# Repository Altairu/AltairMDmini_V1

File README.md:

# AltairMDmini_V1
AltairMDmini_V1

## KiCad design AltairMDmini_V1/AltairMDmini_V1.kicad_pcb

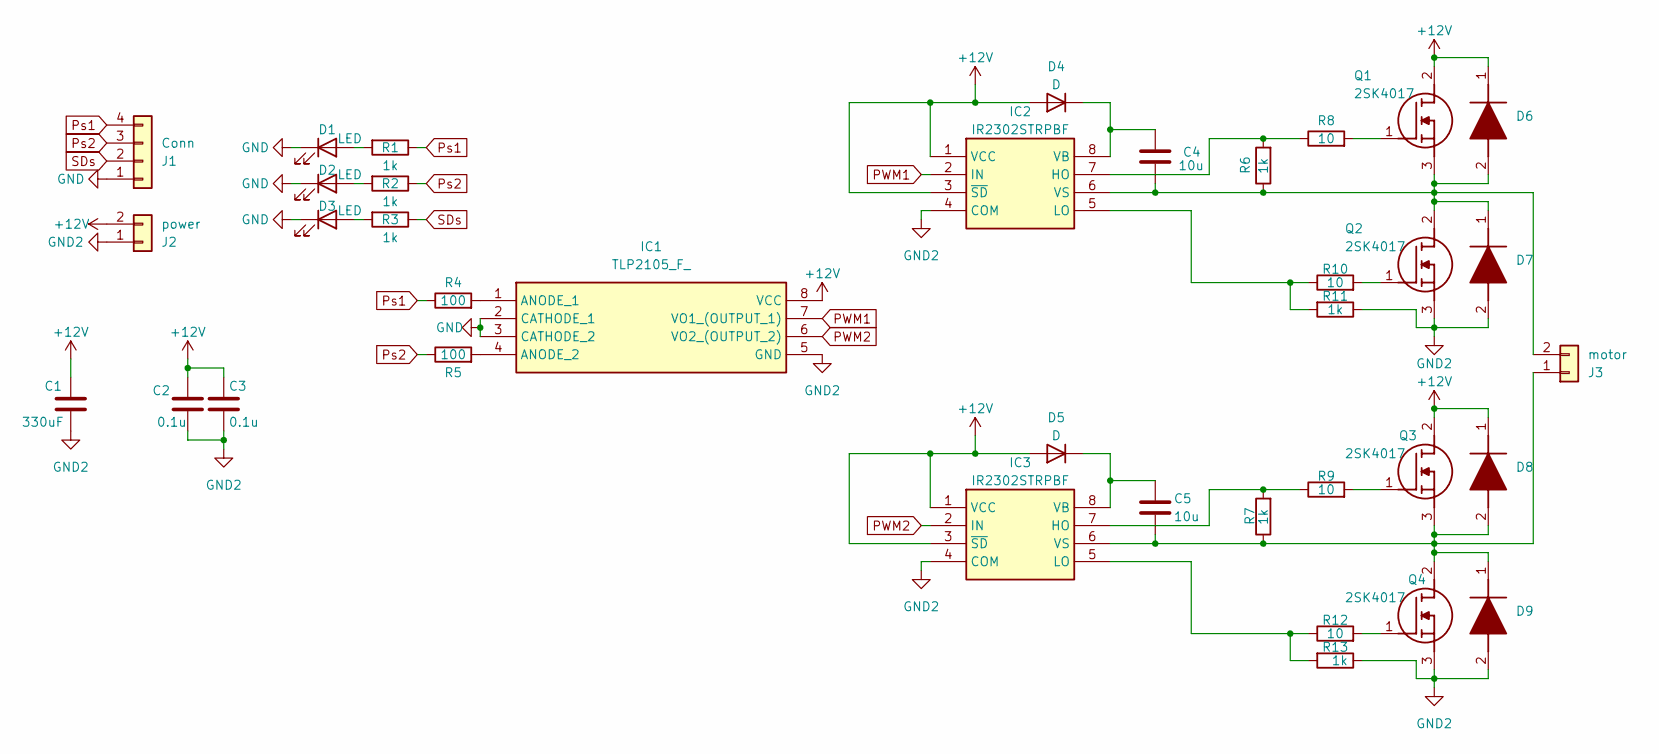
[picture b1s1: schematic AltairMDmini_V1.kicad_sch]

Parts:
C1: 330uF; CP_Elec_10x10
C2, C3: 0.1u; C_0603_1608Metric
C4, C5: 10u; C_0603_1608Metric
D1, D2, D3: LED; LED_0603_1608Metric
D4, D5: D; D_0603_1608Metric
D6, D7, D8, D9: RF201LAM2STR; Manufacturer_Part_Number RF201LAM2STR
IC1: TLP2105_F_; SOIC127P600X290-8N; Manufacturer_Part_Number TLP2105(F); Mouser Part Number 757-TLP2105(F)
IC2, IC3: IR2302STRPBF; SOIC127P600X290-8N; Manufacturer_Part_Number IR2302STRPBF
J1: Conn; JST_XA_S04B-XASK-1_1x04_P2.50mm_Horizontal
J2: power; AMASS_XT30PW-M_1x02_P2.50mm_Horizontal
J3: motor; AMASS_XT30PW-F_1x02_P2.50mm_Horizontal
Q1, Q2, Q3, Q4: 2SK4017; TO230P250X650X900-3P; Manufacturer_Part_Number 2SK4017; Mouser Part Number N/A
R1, R2, R3, R6, R7, R11, R13: 1k; R_0603_1608Metric
R4, R5: 100; R_0603_1608Metric
R8, R9, R10, R12: 10; R_0603_1608Metric

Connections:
+12V: C1.1, C2.1, C3.1, D4.2 (A), D5.2 (A), D6.1 (K), D8.1 (K), IC1.8 (VCC), IC2.1 (VCC), IC2.3 (~SD), IC3.1 (VCC), IC3.3 (~SD), J2.2, Q1.2 (D), Q3.2 (D)
GND: D1.1 (K), D2.1 (K), D3.1 (K), IC1.2 (CATHODE_1), IC1.3 (CATHODE_2), J1.1
GND2: C1.2, C2.2, C3.2, D7.2 (A), D9.2 (A), IC1.5 (GND), IC2.4 (COM), IC3.4 (COM), J2.1, Q2.3 (S), Q4.3 (S), R11.1, R13.1
unnamed: D1.2 (A), R1.2
unnamed: D2.2 (A), R2.2
unnamed: D3.2 (A), R3.2
unnamed: C4.1, D4.1 (K), IC2.8 (VB)
unnamed: C5.1, D5.1 (K), IC3.8 (VB)
unnamed: C4.2, D6.2 (A), D7.1 (K), IC2.6 (VS), J3.2, Q1.3 (S), Q2.2 (D), R6.1
unnamed: C5.2, D8.2 (A), D9.1 (K), IC3.6 (VS), J3.1, Q3.3 (S), Q4.2 (D), R7.1
unnamed: IC1.1 (ANODE_1), R4.2
unnamed: IC1.4 (ANODE_2), R5.2
unnamed: IC2.7 (HO), R6.2, R8.1
unnamed: IC2.5 (LO), R10.1, R11.2
unnamed: IC3.7 (HO), R7.2, R9.1
unnamed: IC3.5 (LO), R12.1, R13.2
unnamed: Q1.1 (G), R8.2
unnamed: Q2.1 (G), R10.2
unnamed: Q3.1 (G), R9.2
unnamed: Q4.1 (G), R12.2
PWM1: IC1.7 (VO1_(OUTPUT_1)), IC2.2 (IN)
PWM2: IC1.6 (VO2_(OUTPUT_2)), IC3.2 (IN)
Ps1: J1.4, R1.1, R4.1
Ps2: J1.3, R2.1, R5.1
SDs: J1.2, R3.1

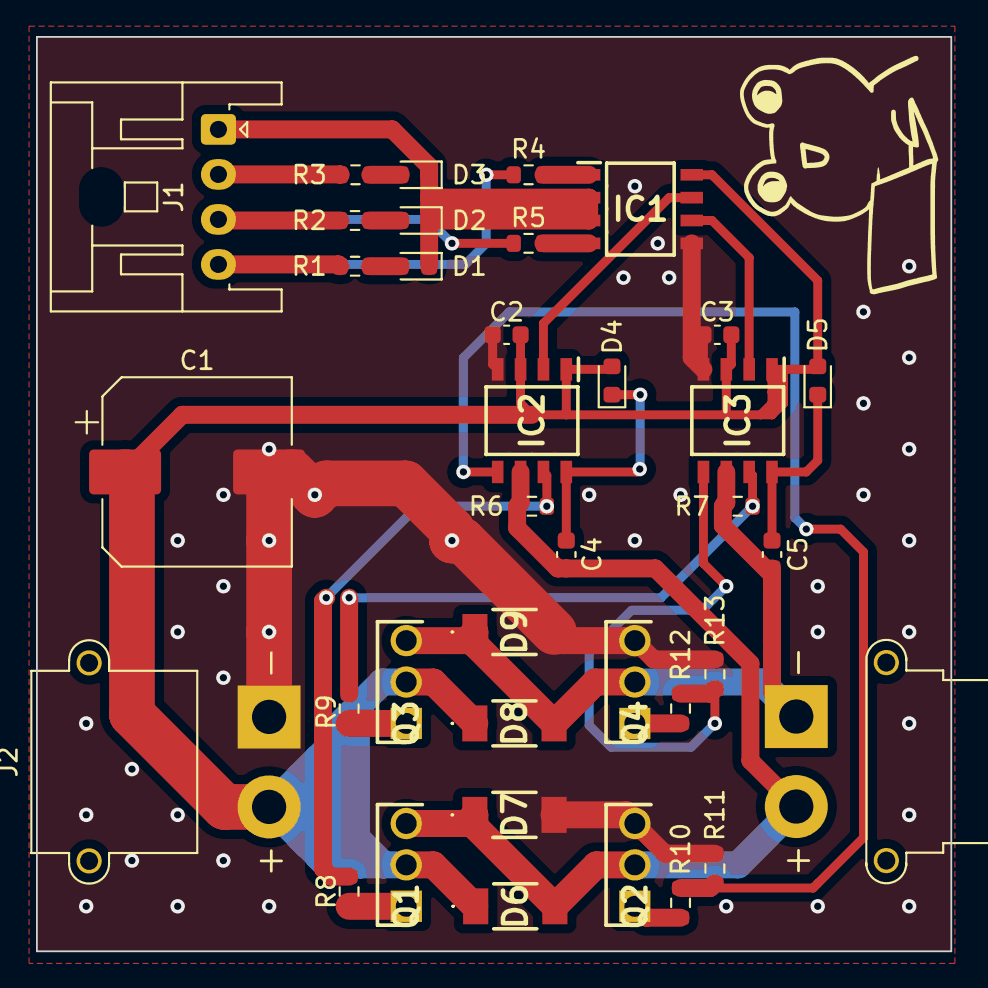
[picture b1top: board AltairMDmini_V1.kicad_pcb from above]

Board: 2 copper layers, 50.8 x 50.8 mm, 37 parts (0 on the bottom side), 25 nets.
